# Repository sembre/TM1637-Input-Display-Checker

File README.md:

# TM1637 Input Display Checker

## 📌 Deskripsi (Bahasa Indonesia)

Proyek ini berfungsi untuk membaca status dari sejumlah pin digital pada board **Arduino** dan menampilkan nomor pin yang **aktif (terhubung ke GND)** ke **7-segmen display TM1637**.  
Selain itu, nomor pin yang aktif juga akan ditampilkan pada **Serial Monitor**.

🔌 **Fungsi utama:**
- Memeriksa banyak pin input digital secara otomatis.
- Menampilkan nomor pin yang aktif pada **TM1637 7-segmen**.
- Mengirim informasi pin aktif ke **Serial Monitor**.
- Menggunakan **INPUT_PULLUP** sehingga tidak memerlukan resistor eksternal.

---

## 📘 Description (English)

This project reads the status of multiple digital input pins on an **Arduino** board and displays the number of the pin that is **active (connected to GND)** on a **TM1637 7-segment display**.  
Additionally, the active pin number is also printed to the **Serial Monitor**.

🔌 **Main features:**
- Automatically scans multiple digital input pins.
- Displays the active pin number on a **TM1637 display**.
- Sends active pin info to the **Serial Monitor**.
- Uses **INPUT_PULLUP** to eliminate the need for external resistors.

---

## 🛠️ Hardware Requirements

- Arduino Mega / Uno  
- TM1637 7-segment display module  
- Jumper cables  
- GND switch or test pins  

---

## 🔌 Wiring (TM1637)

| TM1637 Pin | Arduino Pin |
|------------|--------------|
| CLK        | A0           |
| DIO        | A1           |
| VCC        | 5V           |
| GND        | GND          |

> ⚠️ Setiap pin input menggunakan `INPUT_PULLUP`, jadi cukup hubungkan ke **GND** untuk membacanya sebagai aktif.

---

## 📁 File

- `cek_pin_MAX-37.ino` – File utama Arduino yang menjalankan logika pembacaan pin dan tampilan TM1637.

---

## ▶️ Cara Menggunakan (Usage)

1. Sambungkan TM1637 ke Arduino sesuai tabel wiring di atas.  
2. Upload kode `cek_pin_MAX-37.ino` ke Arduino menggunakan Arduino IDE.  
3. Buka **Serial Monitor** dengan baud rate `9600`.  
4. Hubungkan salah satu pin input ke **GND**.  
5. Nomor pin aktif akan muncul di **display TM1637** dan **Serial Monitor**.

---

## 📜 Lisensi (License)

**Creative Commons Attribution 4.0 International (CC BY 4.0)**  
🔗 [https://creativecommons.org/licenses/by/4.0/](https://creativecommons.org/licenses/by/4.0/)

📌 Anda **bebas** menggunakan, membagikan, memodifikasi, dan mendistribusikan kode ini — termasuk untuk tujuan komersial — **selama mencantumkan atribusi** kepada penulis asli.

📎 **Atribusi wajib:**  
Penulis: [AGUS FITRIYANTO](https://github.com/sembre)  
GitHub: [https://github.com/sembre](https://github.com/sembre)

---

## 🤝 Kontribusi (Contributing)

Pull request dan kontribusi sangat diterima!  
Jika Anda menemukan bug atau ingin menambahkan fitur baru, silakan buat *issue* atau kirim *PR* di repository ini.

---

## 📧 Kontak (Contact)

📍 Author: **AGUS FITRIYANTO**  
🔗 GitHub: [https://github.com/sembre](https://github.com/sembre)  

---
## 🦅 File Eagle (Desain PCB/Schematics)

Jika Anda ingin membuat PCB atau melihat skematik, tersedia file Eagle (.sch dan .brd):

- `cek pin 37.sch` – Skematik rangkaian Eagle
- `cek pin 37.brd` – File layout PCB Eagle

### Cara Menggunakan File Eagle

1. Buka file `.sch` atau `.brd` menggunakan **Autodesk Eagle** versi terbaru atau yang kompatibel.
2. Anda dapat memodifikasi desain sesuai kebutuhan, melakukan routing, atau langsung mencetak layout untuk produksi PCB.
3. File ini dapat digunakan sebagai referensi wiring atau untuk pembuatan PCB custom.

> Jika Anda belum memiliki Eagle, Anda bisa mengunduhnya secara gratis untuk penggunaan hobi dari [Autodesk Eagle Official](https://www.autodesk.com/products/eagle/free-download).

---

✨ **Happy coding and hacking!**

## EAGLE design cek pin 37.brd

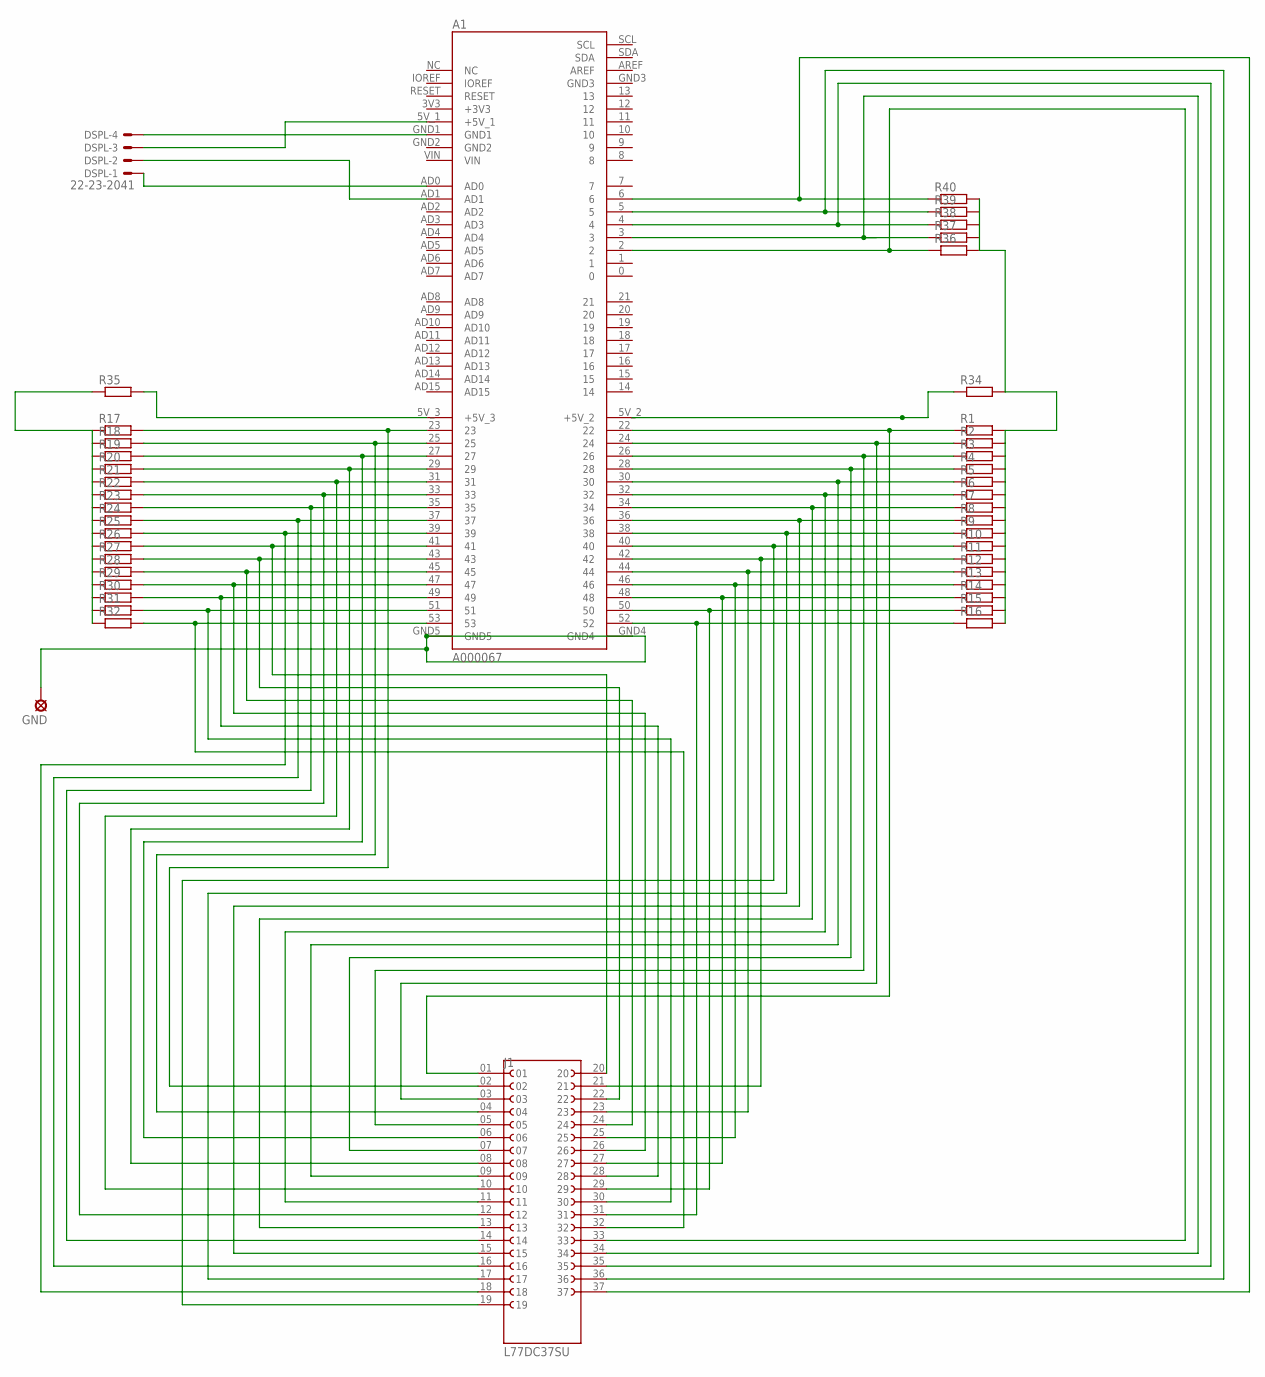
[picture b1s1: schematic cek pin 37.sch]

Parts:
A1: A000067; ARDUINO_A000067
DSPL: 22-23-2041
GND: LSP10
J1: L77DC37SU; AMPHENOL_L77DC37SU
R1, R2, R3, R4, R5, R6, R7, R8, R9, R10, R11, R12, R13, R14, R15, R16, R17, R18, R19, R20, R21, R22, R23, R24, R25, R26, R27, R28, R29, R30, R31, R32, R34, R35, R36, R37, R38, R39, R40: R-EU_0207/12; 0207/12

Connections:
unnamed: A1.23, J1.02, R17.2
unnamed: A1.25, J1.04, R18.2
unnamed: A1.27, J1.06, R19.2
unnamed: A1.29, J1.08, R20.2
unnamed: A1.31, J1.10, R21.2
unnamed: A1.33, J1.12, R22.2
unnamed: A1.35, J1.14, R23.2
unnamed: A1.37, J1.16, R24.2
unnamed: A1.39, J1.18, R25.2
unnamed: A1.41, J1.20, R26.2
unnamed: A1.43, J1.22, R27.2
unnamed: A1.45, J1.24, R28.2
unnamed: A1.47, J1.26, R29.2
unnamed: A1.49, J1.28, R30.2
unnamed: A1.51, J1.30, R31.2
unnamed: A1.53, J1.32, R32.2
unnamed: A1.22, J1.01, R1.1
unnamed: A1.24, J1.03, R2.1
unnamed: A1.26, J1.05, R3.1
unnamed: A1.28, J1.07, R4.1
unnamed: A1.30, J1.09, R5.1
unnamed: A1.32, J1.11, R6.1
unnamed: A1.34, J1.13, R7.1
unnamed: A1.36, J1.15, R8.1
unnamed: A1.5V_1 (+5V_1), DSPL.3
unnamed: A1.GND1, DSPL.4
unnamed: A1.AD1, DSPL.2
unnamed: A1.44, J1.23, R12.1
unnamed: A1.46, J1.25, R13.1
unnamed: A1.48, J1.27, R14.1
unnamed: A1.50, J1.29, R15.1
unnamed: A1.52, J1.31, R16.1
unnamed: A1.38, J1.17, R9.1
unnamed: A1.5V_3 (+5V_3), R35.2
unnamed: A1.2, J1.33, R36.1
unnamed: A1.AD0, DSPL.1
unnamed: A1.4, J1.35, R38.1
unnamed: A1.5, J1.36, R39.1
unnamed: A1.6, J1.37, R40.1
unnamed: R1.2, R2.2, R3.2, R4.2, R5.2, R6.2, R7.2, R8.2, R9.2, R10.2, R11.2, R12.2, R13.2, R14.2, R15.2, R16.2, R34.2, R36.2, R37.2, R38.2, R39.2, R40.2
unnamed: R17.1, R18.1, R19.1, R20.1, R21.1, R22.1, R23.1, R24.1, R25.1, R26.1, R27.1, R28.1, R29.1, R30.1, R31.1, R32.1, R35.1
unnamed: A1.5V_2 (+5V_2), R34.1
unnamed: A1.40, J1.19, R10.1
unnamed: A1.42, J1.21, R11.1
unnamed: A1.GND4, A1.GND5, GND.MP
unnamed: A1.3, J1.34, R37.1

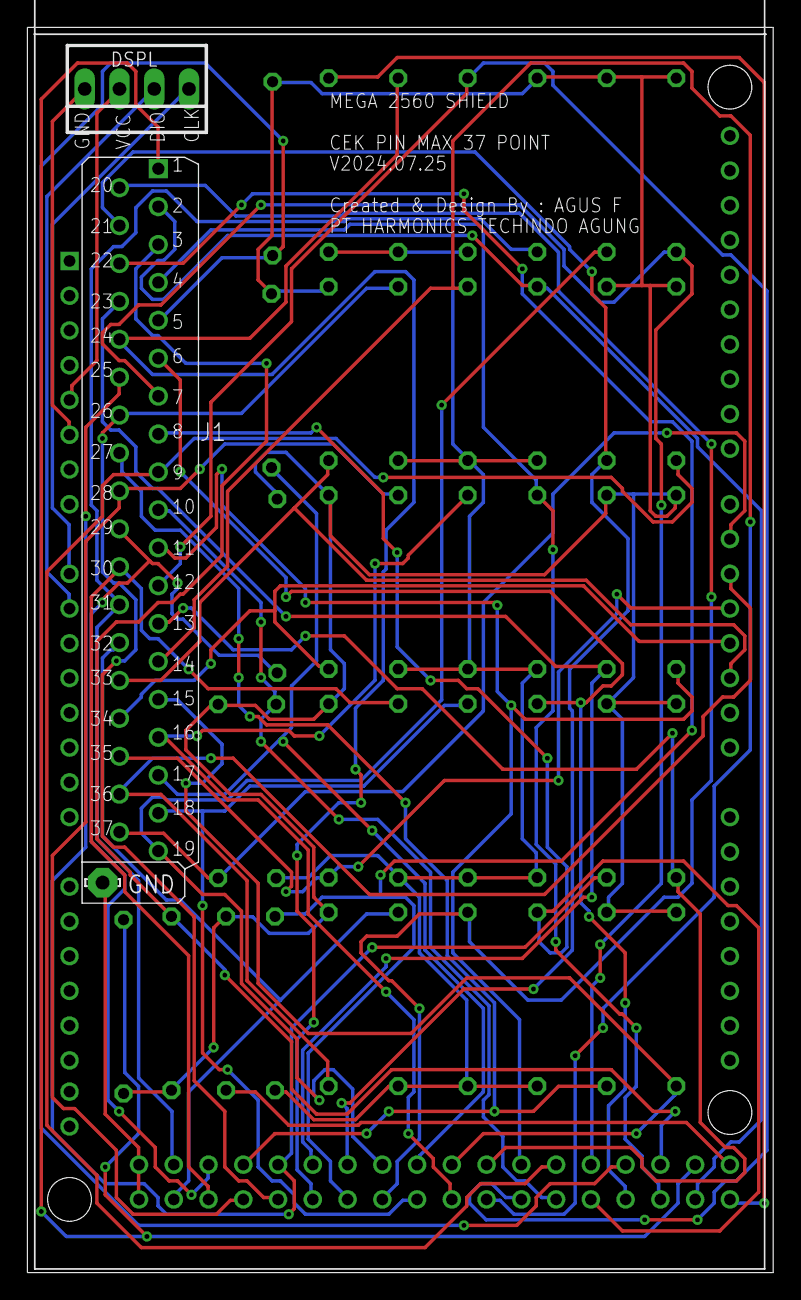
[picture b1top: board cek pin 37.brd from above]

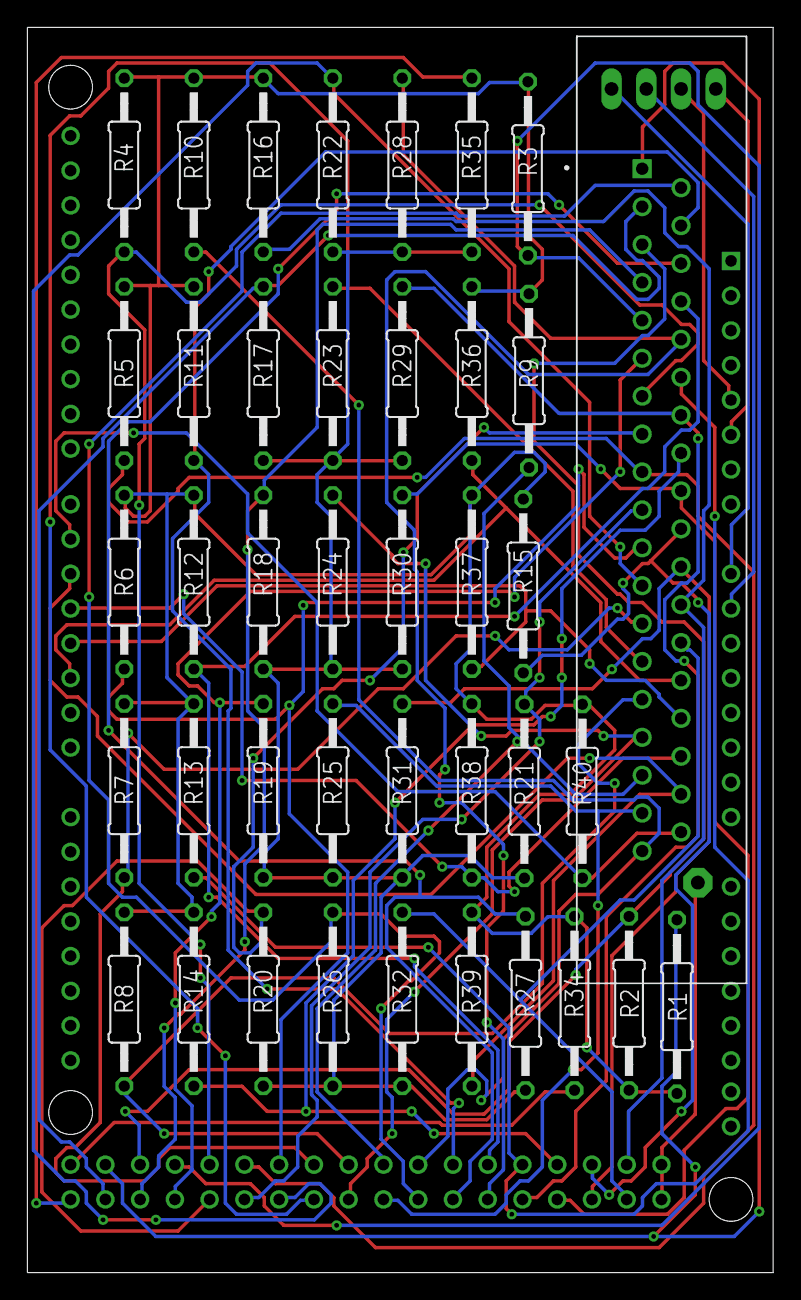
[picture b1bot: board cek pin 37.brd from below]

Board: 2 copper layers, 54.5 x 91.0 mm, 43 parts (40 on the bottom side), 46 nets.

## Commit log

2025-10-01 Enhance README with comprehensive project details
    Updated README to include detailed project description, features, hardware requirements, wiring instructions, usage steps, license information, contribution guidelines, and contact details.
2025-10-01 Update file name in README for Arduino code
2025-10-01 Document Eagle files and usage in README
    Added section for Eagle files and usage instructions.
2025-10-04 Implement boot counter and device lock features
    Added boot counter functionality with EEPROM storage and device lock feature. Updated code to display 'dIE' message when the maximum boot count is reached.
